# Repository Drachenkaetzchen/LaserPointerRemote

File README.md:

A small handheld remote to signal the BDSM traffic light signal (red, yellow, green) to signal if the top should go ahead or not. The signal is transmitted via RFM12 and displayed via LEDs. Incoming signals are additionally signaled by a vibration motor.

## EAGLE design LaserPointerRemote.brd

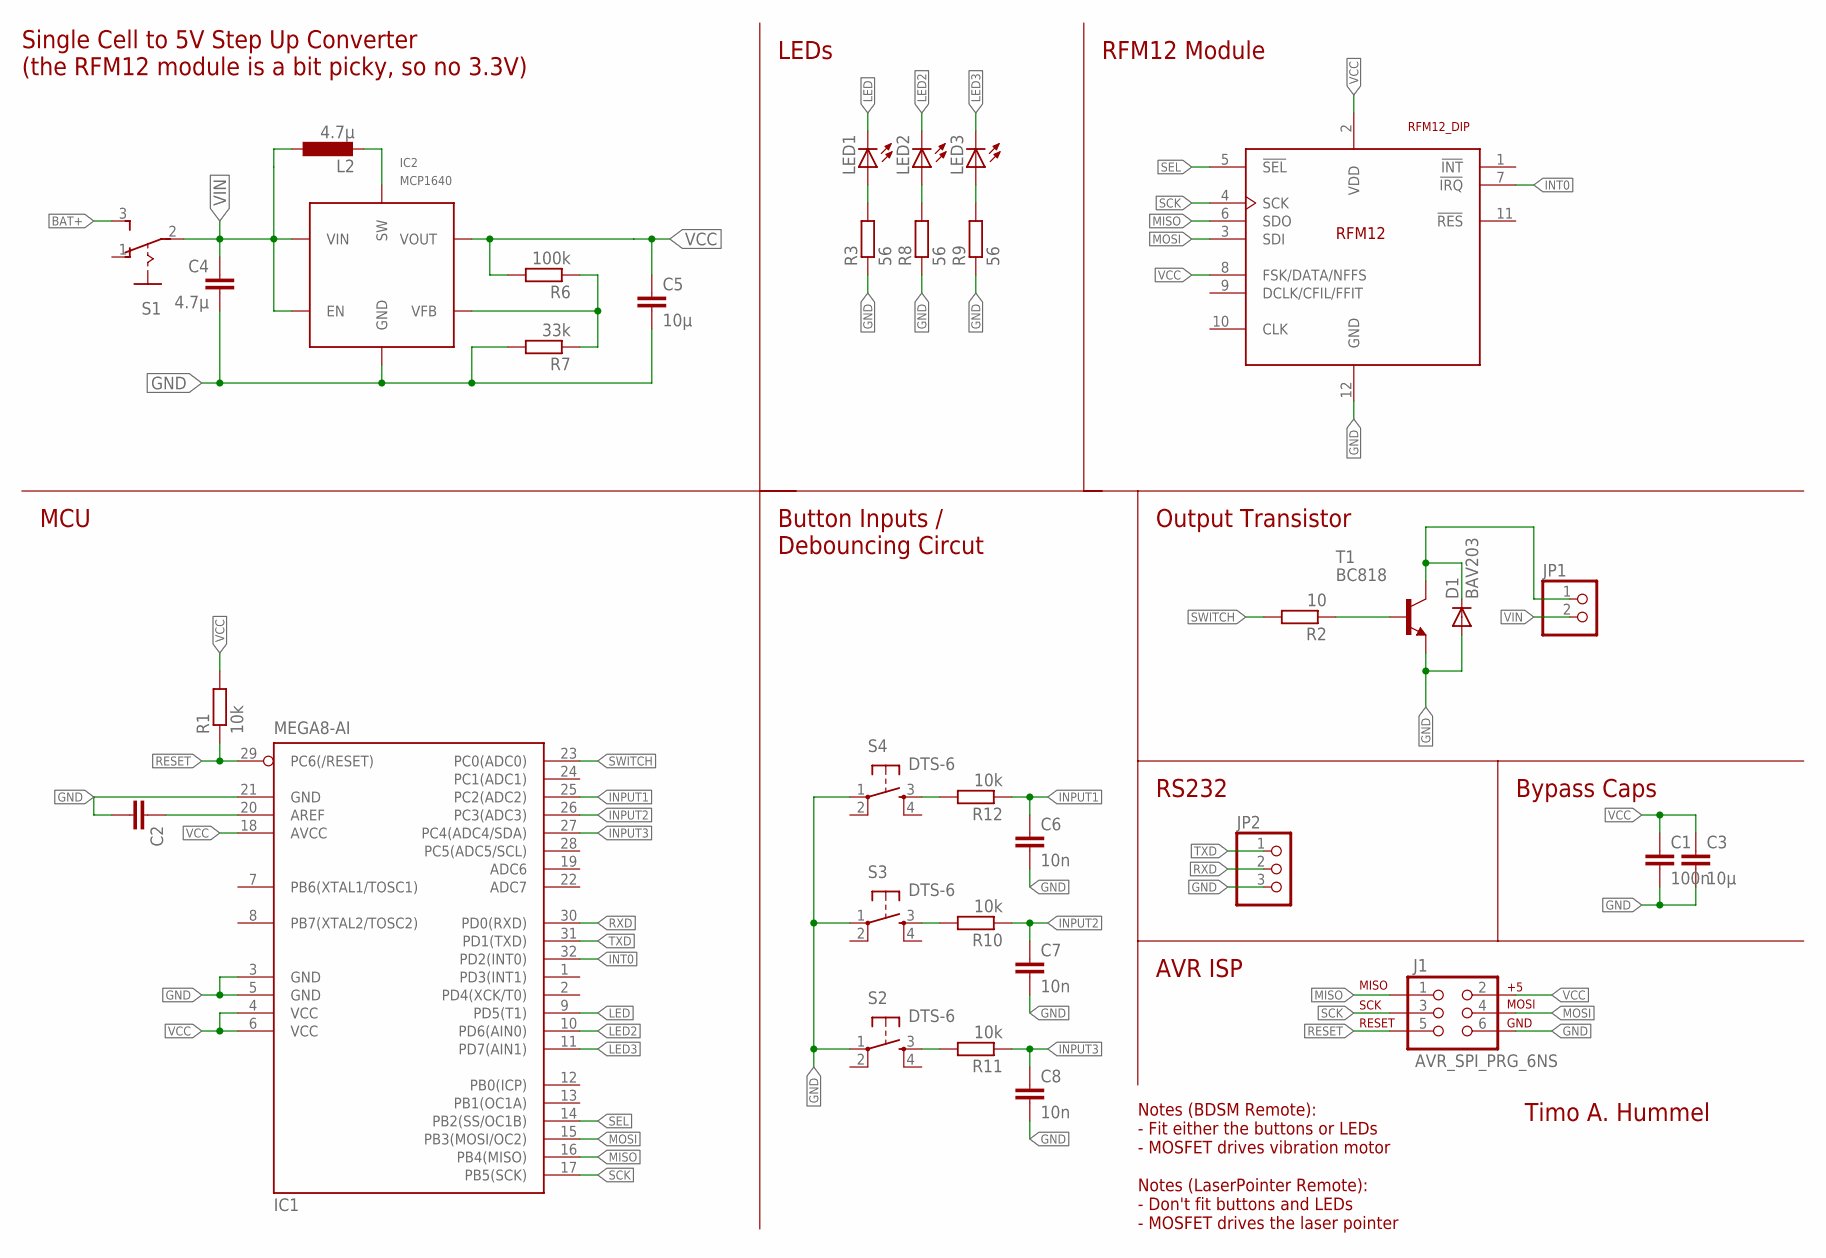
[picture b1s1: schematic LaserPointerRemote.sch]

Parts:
C1: 100n; C0805
C2: C-EUC0805; C0805
C3, C5: 10µ; C0805
C4: 4.7µ; C0805
C6, C7, C8: 10n; C0805
D1: BAV203; SOD80C
IC1: MEGA8-AI; TQFP32-08
IC2: MCP1640; SOT23-6
J1: AVR_SPI_PRG_6NS; 2X3-NS
JP1: PINHD-1X2; 1X02
JP2: PINHD-1X3; 1X03
L2: 4.7µ; PISG
LED1, LED2, LED3: LED3MM
R1, R10, R11, R12: 10k; R0805
R2: 10; R0805
R3, R8, R9: 56; R0805
R6: 100k; R0805
R7: 33k; R0805
S1: SS12; NKKSS-12
S2, S3, S4: DTS-6
T1: BC818; SOT23-BEC
U$1: RFM12_DIP; DIL-2MM-2X06

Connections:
BAT+: S1.3 (S)
GND: C1.2, C2.2, C3.2, C4.2, C5.2, C6.2, C7.2, C8.2, D1.A, IC1.3 (GND), IC1.5 (GND), IC1.21 (GND), IC2.2 (GND), J1.6, JP2.3, R3.1, R7.2, R8.1, R9.1, S2.1, S3.1, S4.1, T1.E, U$1.12 (GND)
INPUT1: C6.1, IC1.25 (PC2(ADC2)), R12.1
INPUT2: C7.1, IC1.26 (PC3(ADC3)), R10.1
INPUT3: C8.1, IC1.27 (PC4(ADC4/SDA)), R11.1
INT0: IC1.32 (PD2(INT0)), U$1.7 (!IRQ)
LED: IC1.9 (PD5(T1)), LED1.K (C)
LED2: IC1.10 (PD6(AIN0)), LED2.K (C)
LED3: IC1.11 (PD7(AIN1)), LED3.K (C)
MISO: IC1.16 (PB4(MISO)), J1.1, U$1.6 (SDO)
MOSI: IC1.15 (PB3(MOSI/OC2)), J1.4, U$1.3 (SDI)
unnamed: R2.1, T1.B
unnamed: D1.C, JP1.1, T1.C
unnamed: LED1.A, R3.2
unnamed: C2.1, IC1.20 (AREF)
unnamed: LED2.A, R8.2
unnamed: IC2.1 (SW), L2.2
unnamed: LED3.A, R9.2
unnamed: R12.2, S4.3
unnamed: IC2.4 (VFB), R6.1, R7.1
unnamed: R10.2, S3.3
unnamed: R11.2, S2.3
RESET: IC1.29 (PC6(/RESET)), J1.5, R1.1
RXD: IC1.30 (PD0(RXD)), JP2.2
SCK: IC1.17 (PB5(SCK)), J1.3, U$1.4 (SCK)
SEL: IC1.14 (PB2(SS/OC1B)), U$1.5 (!SEL)
SWITCH: IC1.23 (PC0(ADC0)), R2.2
TXD: IC1.31 (PD1(TXD)), JP2.1
VCC: C1.1, C3.1, C5.1, IC1.4 (VCC), IC1.6 (VCC), IC1.18 (AVCC), IC2.5 (VOUT), J1.2, R1.2, R6.2, U$1.2 (VDD), U$1.8 (FSK/DATA/NFFS)
VIN: C4.1, IC2.3 (EN), IC2.6 (VIN), JP1.2, L2.1, S1.2

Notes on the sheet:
Single Cell to 5V Step Up Converter (the RFM12 module is a bit picky, so no 3.3V)
Timo A. Hummel
MCU
Button Inputs / Debouncing Circut
LEDs
RFM12 Module
Output Transistor
RS232
Bypass Caps
AVR ISP
Notes (BDSM Remote): - Fit either the buttons or LEDs - MOSFET drives vibration motor Notes (LaserPointer Remote): - Don't fit buttons and LEDs - MOSFET drives the laser pointer

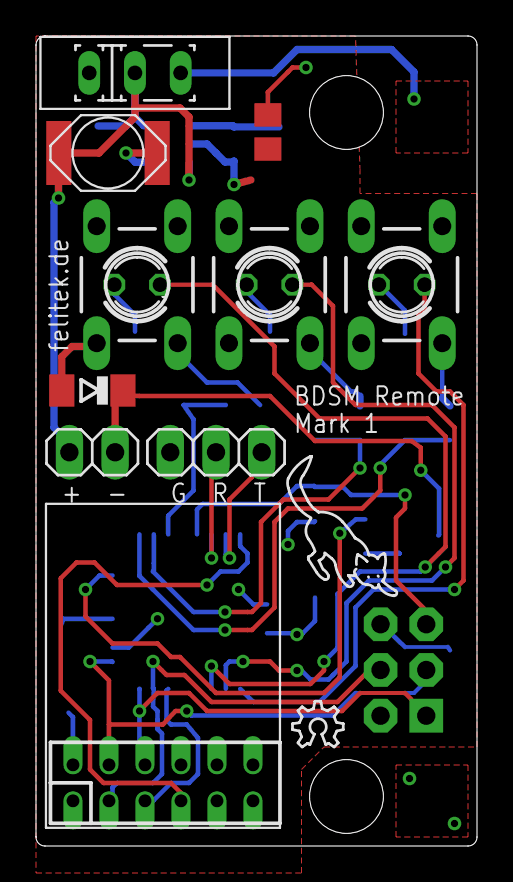
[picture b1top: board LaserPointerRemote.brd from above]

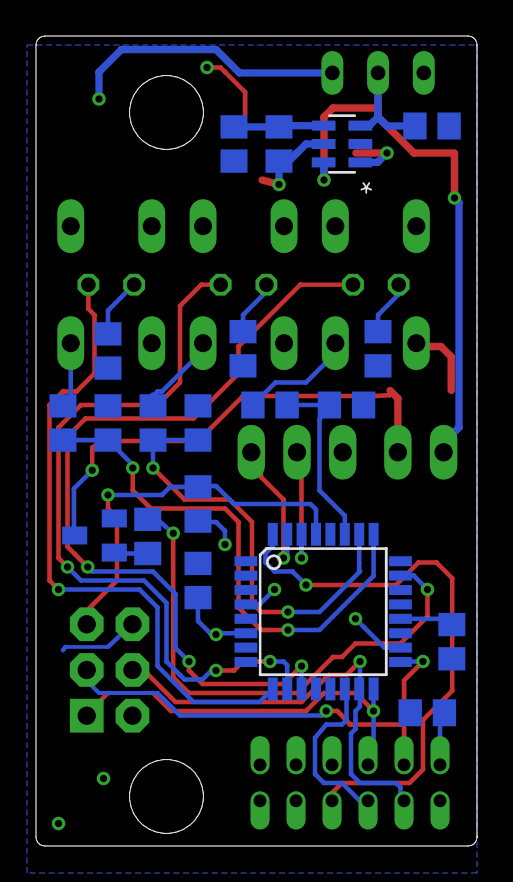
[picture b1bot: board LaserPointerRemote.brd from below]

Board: 2 copper layers, 24.5 x 45.0 mm, 35 parts (20 on the bottom side), 29 nets.

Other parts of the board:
U$2: OSHW_6X100_NOTEXT

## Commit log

2014-05-03 Fixed fonts + adjusted holes
2014-05-17 Refactored PCB to fit the strapupox
2014-06-07 Changed VCC to 5V instead of 3.3V Added NPN transistor instead of mosfet Connected AVCC
2014-06-28 Added readme
2014-06-29 Use X7R output cap instead of a tantalum one

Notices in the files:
parts and their libraries:
SparkFun: Licensing: CC v3.0 Share-Alike You are welcome to use this library for commercial purposes.
